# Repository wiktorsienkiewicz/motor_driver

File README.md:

This board can drive two DC motors in two direction and one motor in one direction.

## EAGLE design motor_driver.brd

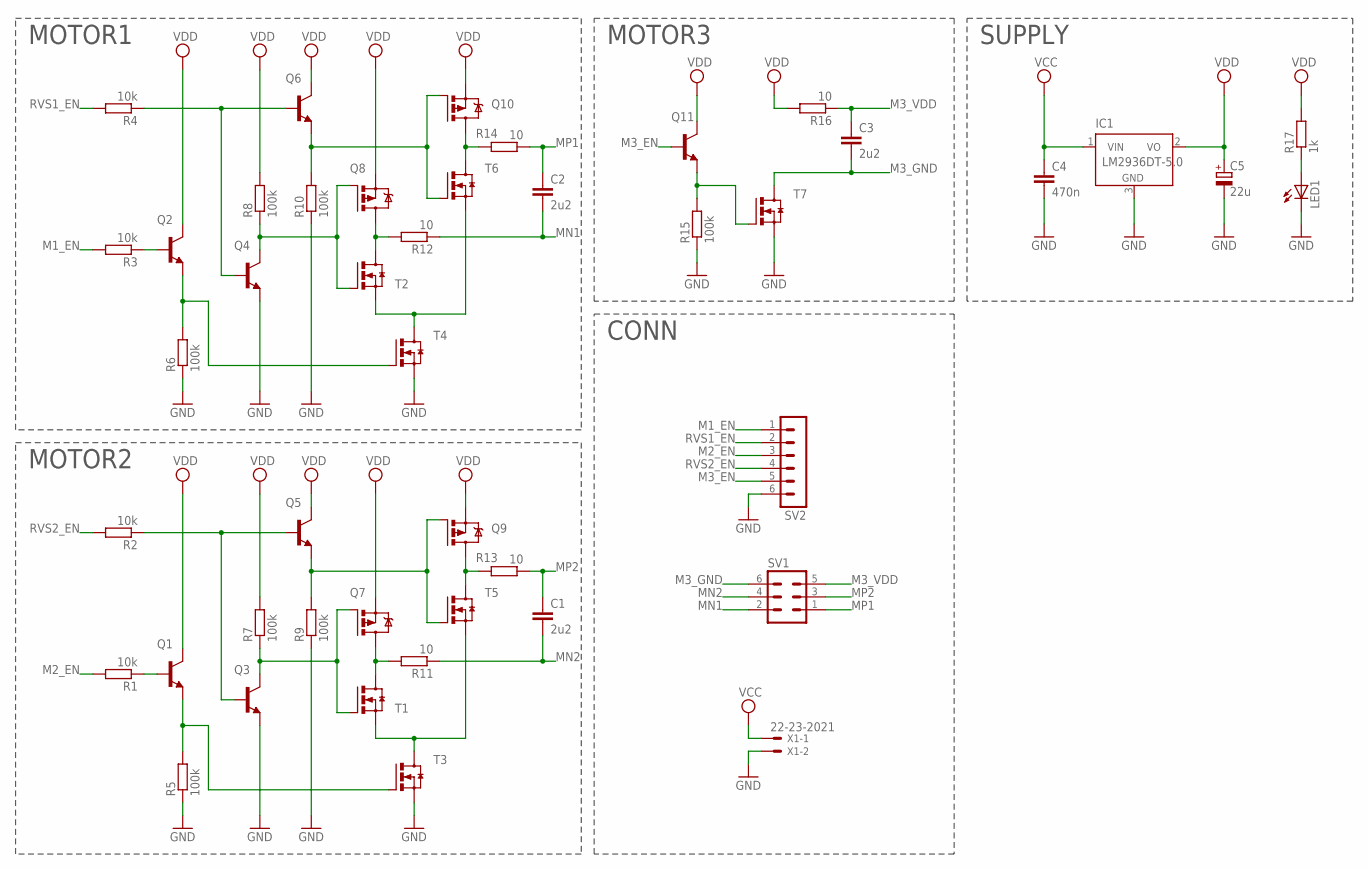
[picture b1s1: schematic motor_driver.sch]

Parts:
C1, C2, C3: 2u2; C025-025X050
C4: 470n; C0805
C5: 22u; 150CLZ-1014
IC1: LM2936DT-5.0; TO252
LED1: LEDCHIPLED_0603; CHIPLED_0603
Q1, Q2, Q3, Q4, Q5, Q6, Q11: BC849SMD; SOT23-BEC
Q7, Q8, Q9, Q10: IRLML5203; MICRO3
R1, R2, R3, R4: 10k; R0603
R5, R6, R7, R8, R9, R10, R15: 100k; R0603
R11, R12, R13, R14: 10; R2512
R16: 10; R0603
R17: 1k; R0603
SV1: MA03-2
SV2: MA06-1
T1, T2, T3, T4, T5, T6, T7: IRLML2803; MICRO3
X1: 22-23-2021

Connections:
GND: C4.2, C5.-, IC1.3 (GND), LED1.C, Q3.E, Q4.E, R5.1, R6.1, R9.1, R10.1, R15.1, SV2.6, T3.2 (S), T4.2 (S), T7.2 (S), X1.2
M1_EN: R3.2, SV2.1
M2_EN: R1.2, SV2.3
M3_EN: Q11.B, SV2.5
M3_GND: C3.2, SV1.6, T7.3 (D)
M3_VDD: C3.1, R16.1, SV1.5
MN1: C2.2, R12.1, SV1.2
MN2: C1.2, R11.1, SV1.4
MP1: C2.1, R14.1, SV1.1
MP2: C1.1, R13.1, SV1.3
unnamed: Q6.E, Q10.1 (G), R10.2, T6.1 (G)
unnamed: Q10.3 (D), R14.2, T6.3 (D)
unnamed: Q8.3 (D), R12.2, T2.3 (D)
unnamed: Q3.B, Q5.B, R2.1
unnamed: Q5.E, Q9.1 (G), R9.2, T5.1 (G)
unnamed: Q2.E, R6.2, T4.1 (G)
unnamed: Q4.B, Q6.B, R4.1
unnamed: Q9.3 (D), R13.2, T5.3 (D)
unnamed: Q7.3 (D), R11.2, T1.3 (D)
unnamed: T2.2 (S), T4.3 (D), T6.2 (S)
unnamed: Q2.B, R3.1
unnamed: T1.2 (S), T3.3 (D), T5.2 (S)
unnamed: Q1.E, R5.2, T3.1 (G)
unnamed: Q1.B, R1.1
unnamed: Q3.C, Q7.1 (G), R7.1, T1.1 (G)
unnamed: Q11.E, R15.2, T7.1 (G)
unnamed: LED1.A, R17.1
unnamed: Q4.C, Q8.1 (G), R8.1, T2.1 (G)
RVS1_EN: R4.2, SV2.2
RVS2_EN: R2.2, SV2.4
VCC: C4.1, IC1.1 (VIN), X1.1
VDD: C5.+, IC1.2 (VO), Q1.C, Q2.C, Q5.C, Q6.C, Q7.2 (S), Q8.2 (S), Q9.2 (S), Q10.2 (S), Q11.C, R7.2, R8.2, R16.2, R17.2

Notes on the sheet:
MOTOR1
MOTOR2
MOTOR3
CONN
SUPPLY

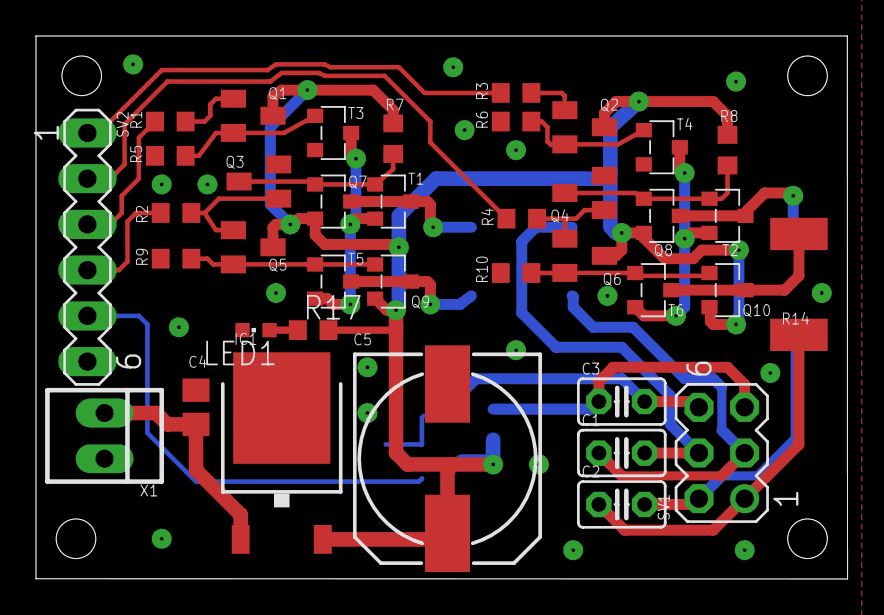
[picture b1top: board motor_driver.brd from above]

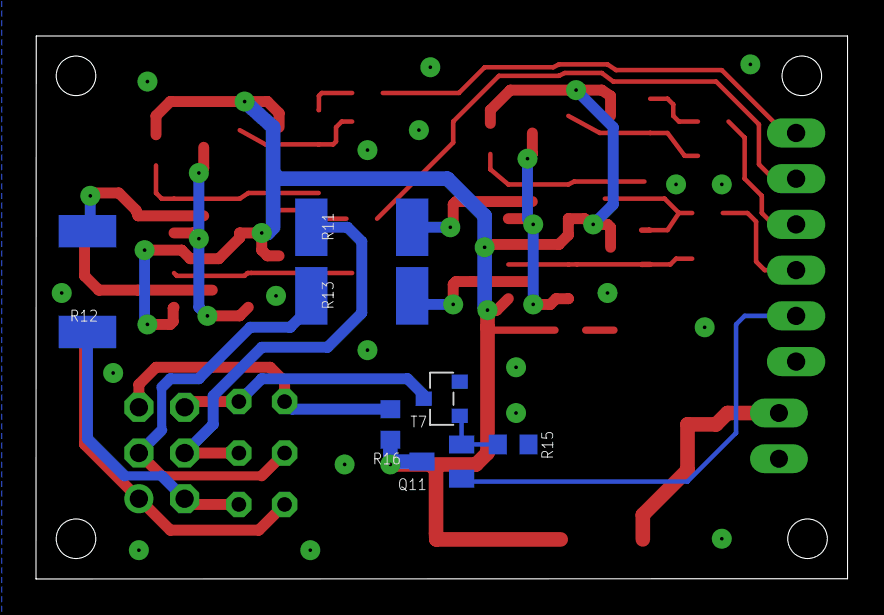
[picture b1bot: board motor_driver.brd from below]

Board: 2 copper layers, 45.1 x 30.2 mm, 45 parts (7 on the bottom side), 32 nets.

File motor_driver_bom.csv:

"Qty";"Value";"Device";"Package";"Parts";"Description";"";
"7";"";"BC849SMD";"SOT23-BEC";"Q1, Q2, Q3, Q4, Q5, Q6, Q11";"NPN Transistor";"";
"7";"";"IRLML2803";"MICRO3";"T1, T2, T3, T4, T5, T6, T7";"HEXFET Power N-Channel MOSFET";"";
"4";"";"IRLML5203";"MICRO3";"Q7, Q8, Q9, Q10";"HEXFET P-Channel Power MOSFET";"";
"1";"";"LEDCHIPLED_0603";"CHIPLED_0603";"LED1";"LED";"";
"1";"";"MA03-2";"MA03-2";"SV1";"PIN HEADER";"";
"1";"";"MA06-1";"MA06-1";"SV2";"PIN HEADER";"";
"1";"10";"R-EU_R0603";"R0603";"R16";"RESISTOR, European symbol";"";
"4";"10";"R-EU_R2512";"R2512";"R11, R12, R13, R14";"RESISTOR, European symbol";"";
"7";"100k";"R-EU_R0603";"R0603";"R5, R6, R7, R8, R9, R10, R15";"RESISTOR, European symbol";"";
"4";"10k";"R-EU_R0603";"R0603";"R1, R2, R3, R4";"RESISTOR, European symbol";"";
"1";"1k";"R-EU_R0603";"R0603";"R17";"RESISTOR, European symbol";"";
"1";"22-23-2021";"22-23-2021";"22-23-2021";"X1";".100" (2.54mm) Center Header - 2 Pin";"";
"1";"22u";"CPOL-EU150CLZ-1014";"150CLZ-1014";"C5";"POLARIZED CAPACITOR, European symbol";"";
"3";"2u2";"C-EU025-025X050";"C025-025X050";"C1, C2, C3";"CAPACITOR, European symbol";"";
"1";"470n";"C-EUC0805";"C0805";"C4";"CAPACITOR, European symbol";"";
"1";"LM2936DT-5.0";"LM2936DT-5.0";"TO252";"IC1";"Ultra-Low Quiescent Current LDO Voltage Regulator";"";

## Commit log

2015-04-08 changed resistors in m1, m2 drivers
2015-04-11 added LED, added bom
